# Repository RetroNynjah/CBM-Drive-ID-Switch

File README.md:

# CBM Drive ID Switch

This is a software controlled device ID switch for Commodore disk drives. It can be installed in any Commodore IEC disk drive but it only makes sense to install it in the drives that lack external DIP switches for ID selection but handy for the 1541 drive and for computers with built-in disk drives such as SX-64, C128D and C128DCR. 

## How it works
There's a microcontroller on the PCB that listens for strings of text on the drive data bus. Once a predefined string of bytes arrives on the bus, it flips the drive ID select pins on the VIA and resets the drive. 
The command that the drive listens for is x@RNDRVID where x is a number representing the drive ID to switch to.
Valid device numbers are 8, 9, 10, 11. In the switch command, these are specified as 8, 9, 0, 1. I.e. 0@RNDRVID is the command for switching to device #10. See the usage section for more information on the command.

## Installation

The installation is quite simple if the VIA chips are socketed. Just remove the correct VIA chip (MOS 6522) indicated in the table below, then install the switch in the socket and install the VIA chip in the switch. There is a notch printed on the top of the switch. This notch should be aligned with the notch on the socket.  
If the VIA is soldered to the PCB you will need to first desolder the VIA and install a socket (unless you want to solder the switch to the PCB which I wouldn't recommend). If you need to remove the VIA chip from the switch, be careful with the compoments on top of the PCB. Don't use any sharp objects to pry the chip out of the headers.

|Model			| VIA			| 
|:-----------:	|:-----------:	|
|1541			| UC3 or UAB1	|
|1571 (in 128D) | U9		  	|
|128DCR			| U106			|
|SX-64			| UBC3			|

## Usage

The device ID can be switched from basic using regular CBM DOS commands or by using DOS wedge commands from JiffyDOS or similar. 
Once the ID has been switched, the ID is saved and the drive will startup with the new ID until the ID is changed again. Resetting or power cycling the drive doesn't affect the saved ID.

In the below examples we switch ID of device #8 to device #9. 

#### From CBM DOS

The easiest command to use to get bytes on the drive bus is the LOAD command but other disk commands can be used too.  
```LOAD "9@RNDRVID",8```  
This generates a file not found error (unless you have a file named 9@RNDRVID ;) ). This error is to be expected and nothing to worry about.  

#### From JiffyDOS
```@"9@RNDRVID",8```  
or activate the drive first using CTRL+D or using @8 and use this command:  
```@9@RNDRVID```

## BOM

|Qty|Identifier |Part						|Comments							|
|---|----------	|---------------------------|-----------------------------------|
| 1 |IC2        |ATmega48A (TQFP32)			|Or compatible						|
| 1 |IC4        |SN74AHCT273NSR (SO20)     	|									|
| 1 |IC5        |SN74AHCT1G04DBVR (SOT23-5)	|									|
| 3 |C1,C2,C5   |100nF 0805    				|Ceramic capacitor					|
| 2 |C3,C4      |30pF 0805					|Ceramic capacitor					|
| 1 |R1         |10kΩ 0805					|									|
| 1 |Y1         |ECS-200-20-3X-TR			|Crystal 20MHz						|
| 2 |			|Female header row 			|20pin 2.54mm (for VIA chip)        |
| 2 |			|Male header row			|20pin 2.54mm (round or flat pins)	|
| 1 |D1			|LED 0805					|Optional							|
| 1 |R2			|560Ω 0805					|Optional							|

You can use any larger pin-compatible ATmega MCU such as ATmega88 or ATmega328.  
All variants seem to work including the not 100% pin-compatible PB version.  
The test points TP1 and TP2 are connected to ATmega pins PC1 and PC2 (Arduino pins A1 and A2) and can possibly be used for debugging or for some external connections.  
The optional LED (D1) and its resistor can also be used for debugging purposes but are difficult to see when VIA is installed so the may as well be left out. 

Installaion in the plastic version of C128D with the 1571 controller board covered by an RF shield requires a low profile switch. Flat stackable headers (Arduino shield headers) soldered from the top side is recommended in this case.  
  
Place a socket under the PCB and insert the stackable header pins through the PCB and solder them in place from the top side. The PCB can be removed from socket after soldering a pin on each end. The angle of the pins can then be adjusted before soldering the rest of the pins.
  
When done, cut off the header part so that only the bottom part of the pins are left.  
I haven't found any 20-pin stackable headers but two 10-pin headers on each side works fine.  

Round machined headers add a few millimeters to the height but is fine in C128DCR, SX-64 and 1541 which all have more headroom.  

## Parallel version
I also made a version with a header for a parallel cable since parallel connections can be made using the same VIA.  

It can be used with SpeedDos ROM+Kernal and a userport adapter such as the one designed by Sven Petersen:  
https://github.com/svenpetersen1965/1541-parallel-adapter-SpeedDOS
The header on the Drive ID Switch has the same pinout as the one on Sven Petersen's 1541 adapter.  
With the proper cable, the parallel interface can also be used for nibble transfers with a Zoomfloppy or similar interface.  

The pin-out of the parallel connector is connected to VIA pins according to the below table.

|Header pin |VIA pin    |
|-----------|-----------|
|1          |CA2 (39)   |
|2          |PA0 (2)    |
|3          |PA1 (3)    |
|4          |PA2 (4)    |
|5          |PA3 (5)    |
|6          |PA4 (6)    |
|7          |PA5 (7)    |
|8          |PA6 (8)    |
|9          |PA7 (9)    |
|10         |CB1 (18)   |

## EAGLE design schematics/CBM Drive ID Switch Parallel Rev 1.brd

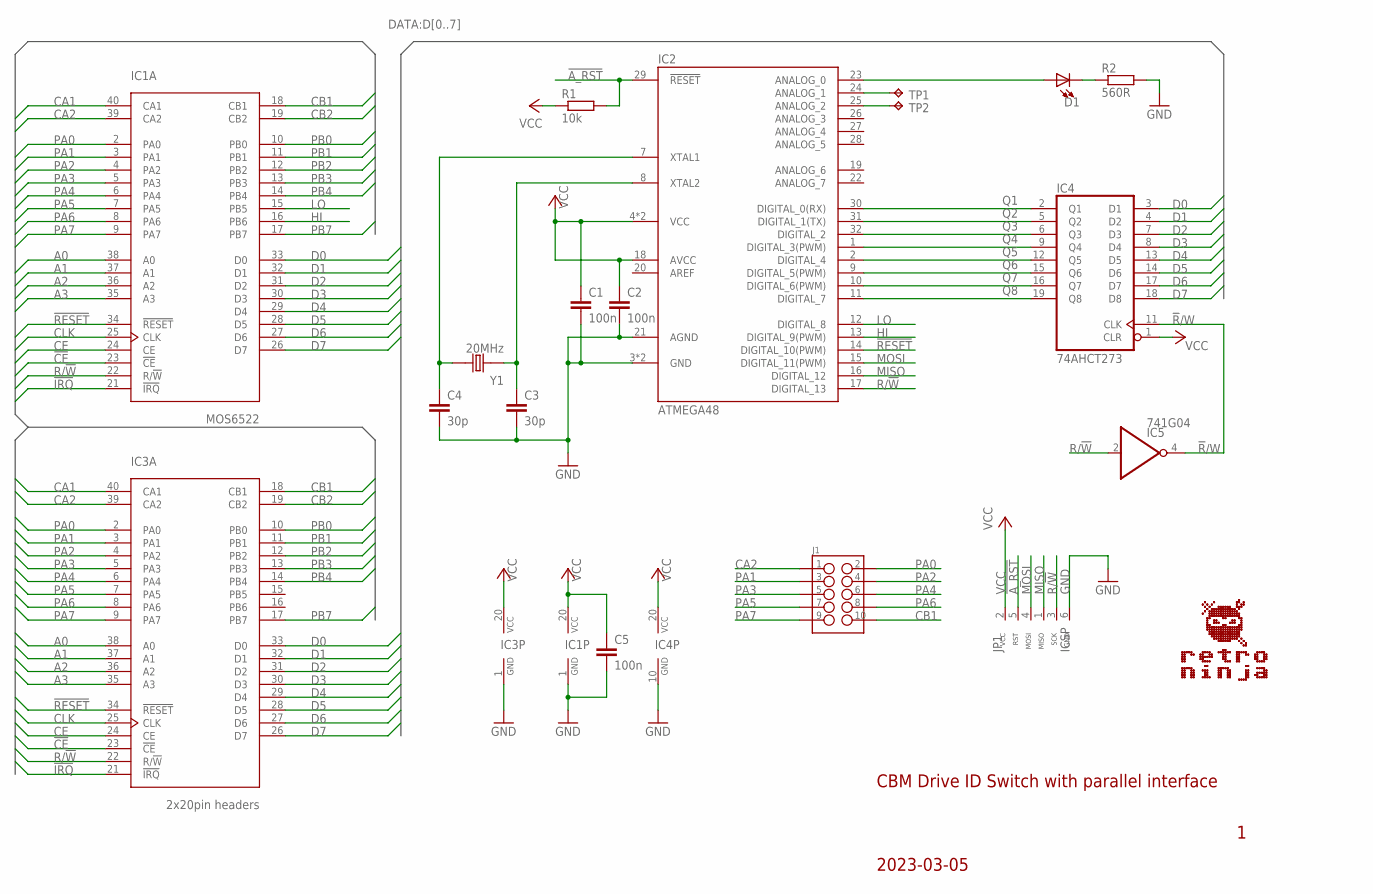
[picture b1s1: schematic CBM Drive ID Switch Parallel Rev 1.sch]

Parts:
C1, C2, C5: 100n; C0805
C3, C4: 30p; C0805
D1: LED_0805; LED0805
IC1: MOS6522; DIL40-6_HEADERS-F
IC2: ATMEGA48; TQFP-32
IC3: 2x20pin headers; DIL40-6_ROUND_BOTTOMPINS
IC4: 74AHCT273; SO20_NARROW
IC5: 741G04; SOT23-5
J1: HEADER_2X5-WALLED-90; HEADER_2X5_WALLED_RIGHT
JP1: ICSP; HEADER_2X3_ALT
R1: 10k; R0805
R2: 560R; R0805
TP1, TP2: TPTP20SQ; TP20SQ
Y1: 20MHz; CRYSTAL_SMD-2_7X4X2.3

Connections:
!A_RST: IC2.29 (!RESET), JP1.5 (RST), R1.2
!CE: IC1.23 (!CE), IC3.23 (!CE)
!IRQ: IC1.21 (!IRQ), IC3.21 (!IRQ)
!R!/W: IC4.11 (CLK), IC5.4 (O)
!RESET: IC1.34 (!RESET), IC2.14 (DIGITAL_10(PWM)), IC3.34 (!RESET)
A0: IC1.38 (A0), IC3.38 (A0)
A1: IC1.37 (A1), IC3.37 (A1)
A2: IC1.36 (A2), IC3.36 (A2)
A3: IC1.35 (A3), IC3.35 (A3)
CA1: IC1.40 (CA1), IC3.40 (CA1)
CA2: IC1.39 (CA2), IC3.39 (CA2), J1.1
CB1: IC1.18 (CB1), IC3.18 (CB1), J1.10
CB2: IC1.19 (CB2), IC3.19 (CB2)
CE: IC1.24 (CE), IC3.24 (CE)
CLK: IC1.25 (CLK), IC3.25 (CLK)
D0: IC1.33 (D0), IC3.33 (D0), IC4.3 (D1)
D1: IC1.32 (D1), IC3.32 (D1), IC4.4 (D2)
D2: IC1.31 (D2), IC3.31 (D2), IC4.7 (D3)
D3: IC1.30 (D3), IC3.30 (D3), IC4.8 (D4)
D4: IC1.29 (D4), IC3.29 (D4), IC4.13 (D5)
D5: IC1.28 (D5), IC3.28 (D5), IC4.14 (D6)
D6: IC1.27 (D6), IC3.27 (D6), IC4.17 (D7)
D7: IC1.26 (D7), IC3.26 (D7), IC4.18 (D8)
GND: C1.2, C2.2, C3.2, C4.2, C5.2, IC1.1 (GND), IC2.3 (GND), IC2.5 (GND), IC2.21 (AGND), IC3.1 (GND), IC4.10 (GND), IC5.3 (GND), JP1.6 (GND), R2.2
HI: IC1.16 (PB6), IC2.13 (DIGITAL_9(PWM))
LO: IC1.15 (PB5), IC2.12 (DIGITAL_8)
MISO: IC2.16 (DIGITAL_12), JP1.1 (MISO)
MOSI: IC2.15 (DIGITAL_11(PWM)), JP1.4 (MOSI)
unnamed: IC2.24 (ANALOG_1), TP1.TP
unnamed: IC2.25 (ANALOG_2), TP2.TP
unnamed: C3.1, IC2.8 (XTAL2), Y1.1
unnamed: C4.1, IC2.7 (XTAL1), Y1.2
unnamed: D1.A, IC2.23 (ANALOG_0)
unnamed: D1.C, R2.1
PA0: IC1.2 (PA0), IC3.2 (PA0), J1.2
PA1: IC1.3 (PA1), IC3.3 (PA1), J1.3
PA2: IC1.4 (PA2), IC3.4 (PA2), J1.4
PA3: IC1.5 (PA3), IC3.5 (PA3), J1.5
PA4: IC1.6 (PA4), IC3.6 (PA4), J1.6
PA5: IC1.7 (PA5), IC3.7 (PA5), J1.7
PA6: IC1.8 (PA6), IC3.8 (PA6), J1.8
PA7: IC1.9 (PA7), IC3.9 (PA7), J1.9
PB0: IC1.10 (PB0), IC3.10 (PB0)
PB1: IC1.11 (PB1), IC3.11 (PB1)
PB2: IC1.12 (PB2), IC3.12 (PB2)
PB3: IC1.13 (PB3), IC3.13 (PB3)
PB4: IC1.14 (PB4), IC3.14 (PB4)
PB7: IC1.17 (PB7), IC3.17 (PB7)
Q1: IC2.30 (DIGITAL_0(RX)), IC4.2 (Q1)
Q2: IC2.31 (DIGITAL_1(TX)), IC4.5 (Q2)
Q3: IC2.32 (DIGITAL_2), IC4.6 (Q3)
Q4: IC2.1 (DIGITAL_3(PWM)), IC4.9 (Q4)
Q5: IC2.2 (DIGITAL_4), IC4.12 (Q5)
Q6: IC2.9 (DIGITAL_5(PWM)), IC4.15 (Q6)
Q7: IC2.10 (DIGITAL_6(PWM)), IC4.16 (Q7)
Q8: IC2.11 (DIGITAL_7), IC4.19 (Q8)
R/!W: IC1.22 (R/!W), IC2.17 (DIGITAL_13), IC3.22 (R/!W), IC5.2 (I), JP1.3 (SCK)
VCC: C1.1, C2.1, C5.1, IC1.20 (VCC), IC2.4 (VCC), IC2.6 (VCC), IC2.18 (AVCC), IC3.20 (VCC), IC4.1 (CLR), IC4.20 (VCC), IC5.5 (VCC), JP1.2 (VCC), R1.1

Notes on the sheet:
2023-03-05
CBM Drive ID Switch with parallel interface

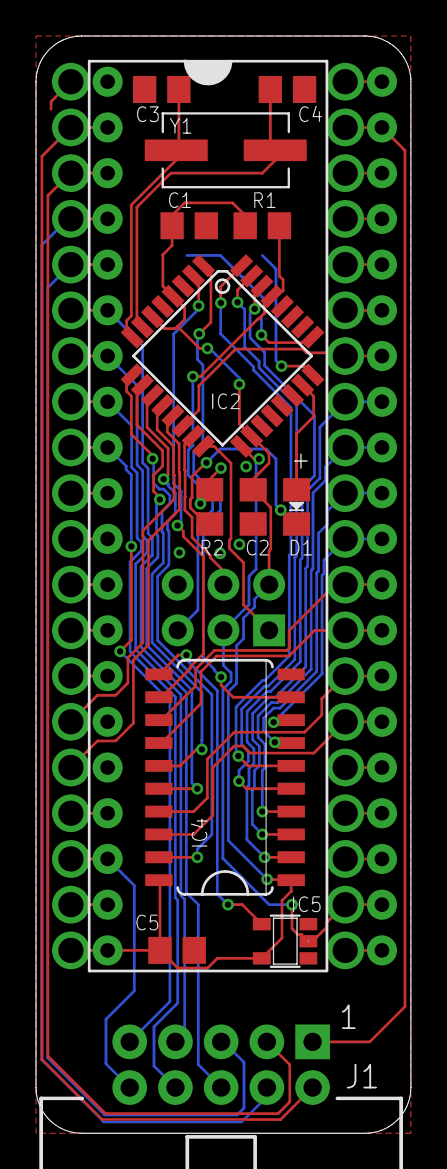
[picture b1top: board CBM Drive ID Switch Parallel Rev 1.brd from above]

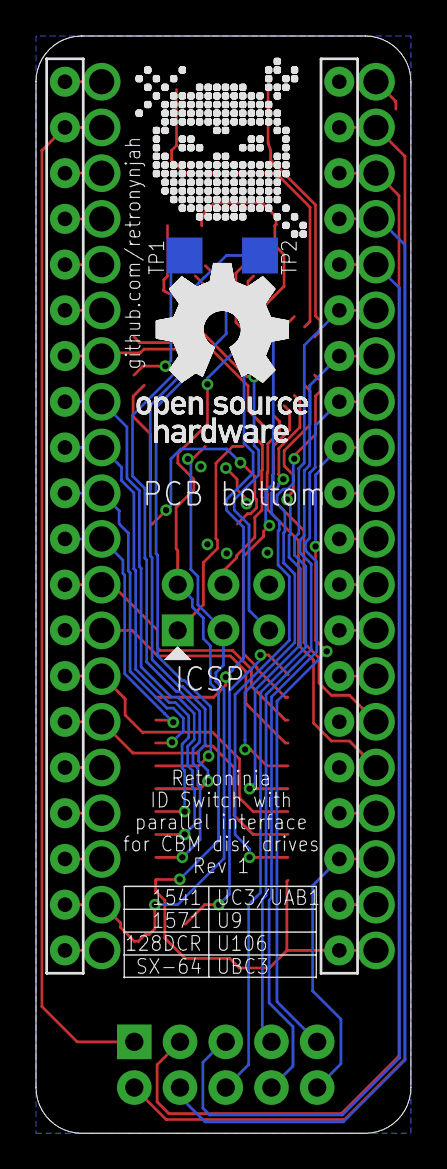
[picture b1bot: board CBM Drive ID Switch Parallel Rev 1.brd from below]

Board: 2 copper layers, 20.8 x 61.0 mm, 20 parts (5 on the bottom side), 58 nets.

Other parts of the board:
U$1: RETRONINJA_NOTEXT_10MM
U$2: OSHW_10MM

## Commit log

2023-02-26 Initial upload
2023-03-19 Schematics corrected
    Pin names corrected. Informational change only
2023-04-01 Added parallel adapter, added images, updated firmware (1.1) and README
    Firmware 1.1 adds a short delay before resetting drive to prevent LOAD commnand from hanging some drives.
2023-04-01 Updated pin header images
